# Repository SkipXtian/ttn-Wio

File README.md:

# GCLora Wio

An Open source weather station that reports tempurature, humidity, barometric pressure and has a RJ11 plug to suit a WH Series tipping bucket rain guage. It has a RFM96 Radio module mounted on the back, transmitting in the 915 - 928 MHz band.</p>

BME280 I2C Address is 0x76<br>
Rain Gauge is on Pin 7 (INT4)<br>

The Arduino example is to connect this Weather station to "The Things Network" through crowd sourced Gateways.
To see a list of gateways head to https://www.thethingsnetwork.org/map </p>

Instructions:

Clone this repo into a directory,<br>
Locate the secrets.h.template file in Arduino/ttn-Wio/<br>
Copy secrets.h.template -> secrets.h and copy details from your TTN console.<br>

This code depends on the lmic library - please make sure you use the version from https://github.com/secluded/arduino-lmic as we made a couple of small changes.
Remove all debugging from config.h for it to compile small enough.

Upload using the Arduino IDE the "Lilypad Arduino USB" board.

In your TTN console you should see data start to arrive. The example is configured to transmit every 5 minutes. You can change this in ttn_Wio.ino, look for TX_INTERVAL = 300; Unit is seconds.

The data should appear in this format: <br>
"32 36 32 38 2C 31 30 31 38 34 36 2C 35 35 34 33 2C 30" Which translates to: <br>
  2  6  2  8  ,  1  0  1  8  4  6  ,  5  5  4  3  ,  0<br>
26.28degress C,      1018.46hPa    ,55.43% Humidity, 0 Rain Ticks

The Tempurature,Barometric and Humidity are divided by 100 to give the decimal places.
Rain Ticks is the count of Rain bucket tipping, multiplying this by 0.2794 will give you rainfall in mm.
We left the processing of Rain for the purpose of indoor use where the sensor might be counting door usage, etc.

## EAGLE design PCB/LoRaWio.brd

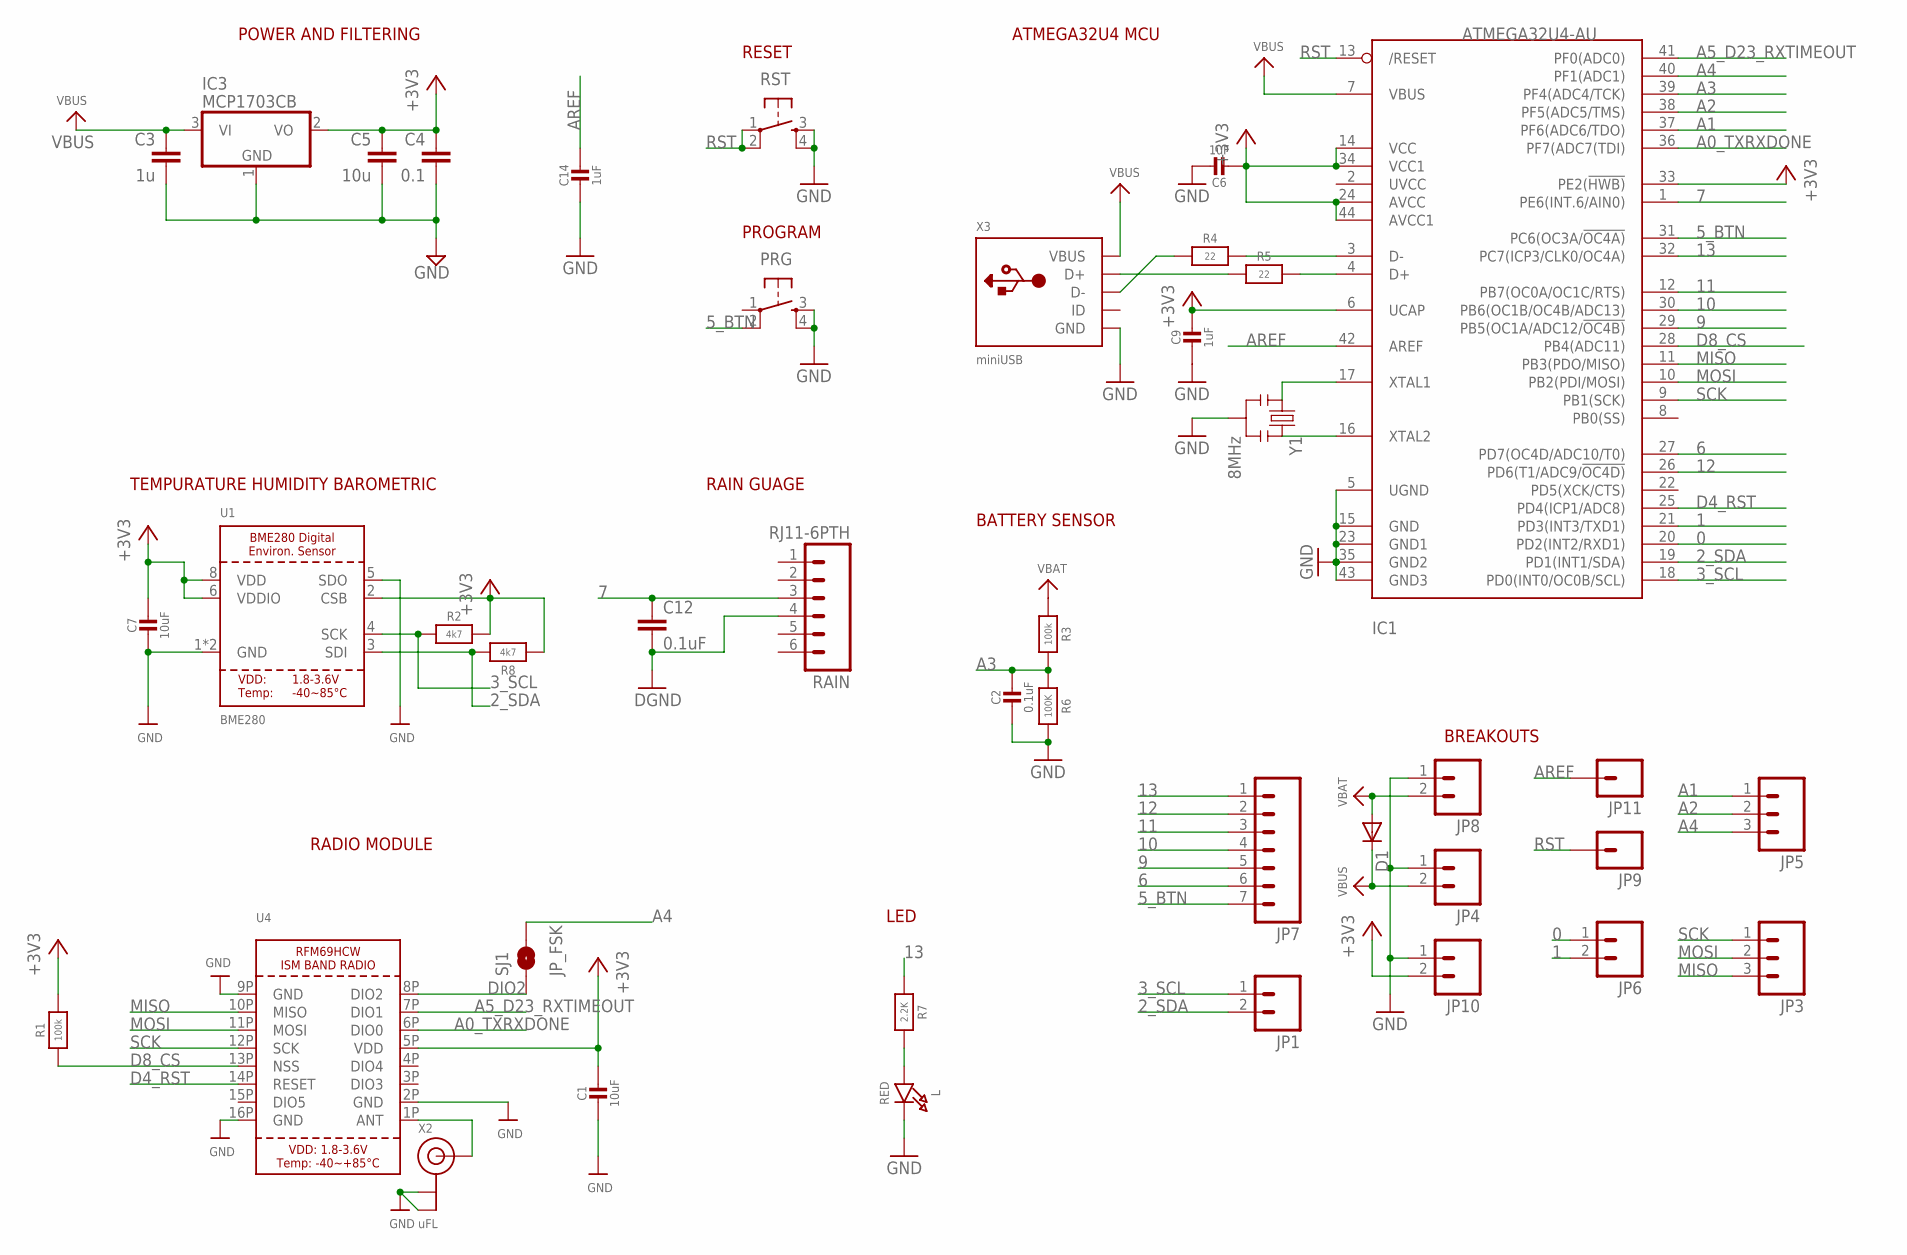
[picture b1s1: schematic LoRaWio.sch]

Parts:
C1, C7: 10uF; 0805-NO
C2: 0.1uF; 0805-NO
C3: 1u; 0805
C4: 0.1; 0805
C5: 10u; 0805-CAP
C6, C9, C14: 1uF; 0805-NO
C12: 0.1uF; 0805
D1: DIODESOD; SOD-323
IC1: ATMEGA32U4-AU; TQFP44
IC3: MCP1703CB; SOT23
JP1, JP4, JP6, JP8, JP10: M021X02_NO_SILK; 1X02_NO_SILK
JP3, JP5: M031X03_NO_SILK; 1X03_NO_SILK
JP7: M07; 1X07
JP9, JP11: M01PTH_NO_SILK_YES_STOP; 1X01_NO_SILK
L: RED; CHIPLED_0805_NOOUTLINE
PRG: TAC_SWITCHSMD; TACTILE_SWITCH_SMD
R1, R3: 100k; 0805-NO@1
R2, R8: 4k7; 0805-NO@1
R4, R5: 22; 0805-NO@1
R6: 100K; 0805-NO@1
R7: 2.2K; 0805-NO@1
RAIN: RJ11-6PTH; RJ11-6
RST: TAC_SWITCHSMD; TACTILE_SWITCH_SMD
SJ1: JP_FSK; SPARKFUN-PASSIVES_SJ_2S-NO
U1: BME280
U4: RFM69HCW_SMT; RFMHCW_SMT
X2: uFL; U.FL
X3: miniUSB; USB-MINIB_LARGER
Y1: 8MHz; RESONATOR-SMD

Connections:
0: IC1.20 (PD2(INT2/RXD1)), JP6.1
1: IC1.21 (PD3(INT3/TXD1)), JP6.2
2_SDA: IC1.19 (PD1(INT1/SDA)), JP1.2, R8.2, U1.3 (SDI)
3_SCL: IC1.18 (PD0(INT0/OC0B/SCL)), JP1.1, R2.1, U1.4 (SCK)
5_BTN: IC1.31 (PC6(OC3A/!OC4A)), JP7.7, PRG.2
6: IC1.27 (PD7(OC4D/ADC10/T0)), JP7.6
7: C12.1, IC1.1 (PE6(INT.6/AIN0)), RAIN.3
9: IC1.29 (PB5(OC1A/ADC12/!OC4B)), JP7.5
10: IC1.30 (PB6(OC1B/OC4B/ADC13)), JP7.4
11: IC1.12 (PB7(OC0A/OC1C/RTS)), JP7.3
12: IC1.26 (PD6(T1/ADC9/!OC4D)), JP7.2
13: IC1.32 (PC7(ICP3/CLK0/OC4A)), JP7.1, R7.1
+3V3: C1.1, C4.1, C5.1, C6.2, C7.1, C9.1, IC1.6 (UCAP), IC1.14 (VCC), IC1.24 (AVCC), IC1.33 (PE2(!HWB)), IC1.34 (VCC1), IC1.44 (AVCC1), IC3.2 (VO), JP10.2, R1.2, R2.2, R8.1, U1.2 (CSB), U1.6 (VDDIO), U1.8 (VDD), U4.5P (VDD)
A0_TXRXDONE: IC1.36 (PF7(ADC7(TDI)), U4.6P (DIO0)
A1: IC1.37 (PF6(ADC6/TDO)), JP5.1
A2: IC1.38 (PF5(ADC5/TMS)), JP5.2
A3: C2.1, IC1.39 (PF4(ADC4/TCK)), R3.2, R6.1
A4: IC1.40 (PF1(ADC1)), JP5.3, SJ1.2
A5_D23_RXTIMEOUT: IC1.41 (PF0(ADC0)), U4.7P (DIO1)
ANT: U4.1P (ANT), X2.3 (SIGNAL)
AREF: C14.1, IC1.42 (AREF), JP11.1
D4_RST: IC1.25 (PD4(ICP1/ADC8)), U4.14P (RESET)
D8_CS: IC1.28 (PB4(ADC11)), R1.1, U4.13P (NSS)
D+: IC1.4 (D+), R5.2
D-: IC1.3 (D-), R4.2
DIO2: SJ1.1, U4.8P (DIO2)
GND: C1.2, C2.2, C3.2, C4.2, C5.2, C6.1, C7.2, C9.2, C12.2, C14.2, IC1.5 (UGND), IC1.15 (GND), IC1.23 (GND1), IC1.35 (GND2), IC1.43 (GND3), IC3.1 (GND), JP4.1, JP8.1, JP10.1, L.C, PRG.3, PRG.4, R6.2, RAIN.4, RST.3, RST.4, U1.1 (GND), U1.5 (SDO), U1.7 (GND), U4.2P (GND), U4.9P (GND), U4.16P (GND), X2.1 (GND), X2.2 (GND), X3.GND, X3.GND1 (GND), X3.GND2 (GND), X3.GND3 (GND), X3.GND4 (GND), Y1.2
MISO: IC1.11 (PB3(PDO/MISO)), JP3.3, U4.10P (MISO)
MOSI: IC1.10 (PB2(PDI/MOSI)), JP3.2, U4.11P (MOSI)
unnamed: L.A, R7.2
unnamed: IC1.16 (XTAL2), Y1.3
unnamed: IC1.17 (XTAL1), Y1.1
unnamed: R5.1, X3.D+
unnamed: R4.1, X3.D-
RST: IC1.13 (/RESET), JP9.1, RST.1, RST.2
SCK: IC1.9 (PB1(SCK)), JP3.1, U4.12P (SCK)
VBAT: D1.2 (A), JP8.2, R3.1
VBUS: C3.1, D1.1 (C), IC1.7 (VBUS), IC3.3 (VI), JP4.2, X3.VBUS

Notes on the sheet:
POWER AND FILTERING
RESET
ATMEGA32U4 MCU
BREAKOUTS
RADIO MODULE
PROGRAM
RAIN GUAGE
TEMPURATURE HUMIDITY BAROMETRIC
LED
BATTERY SENSOR

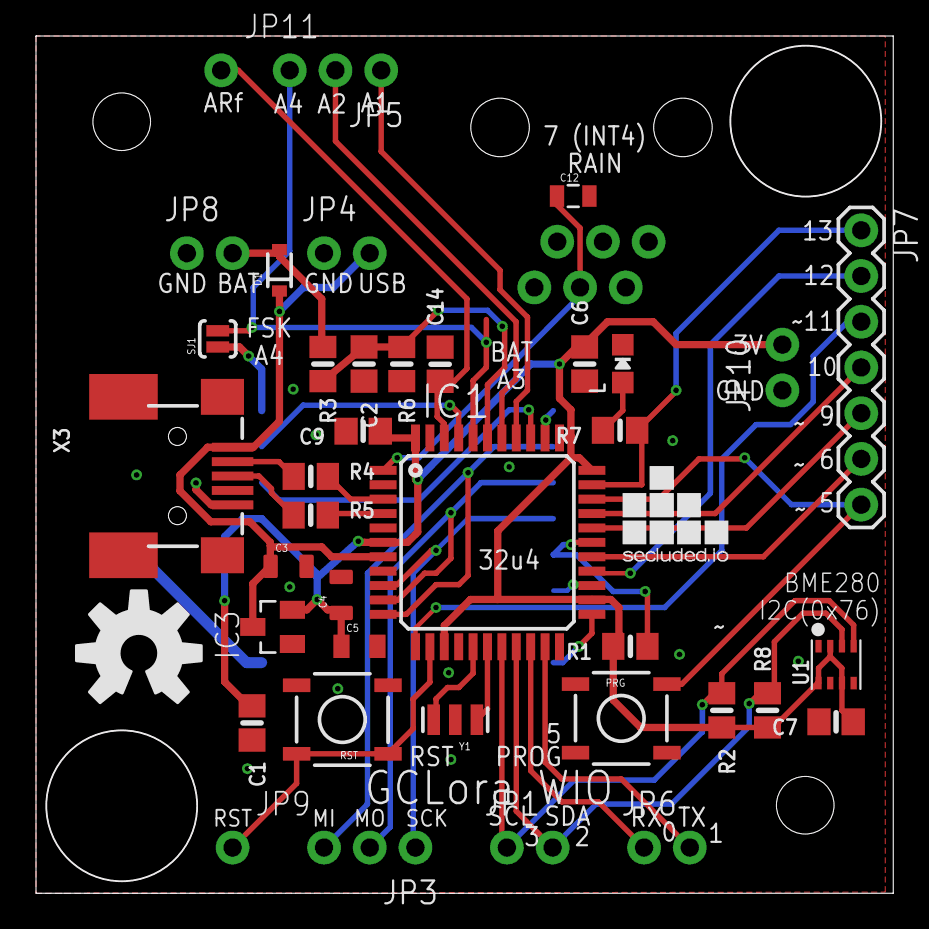
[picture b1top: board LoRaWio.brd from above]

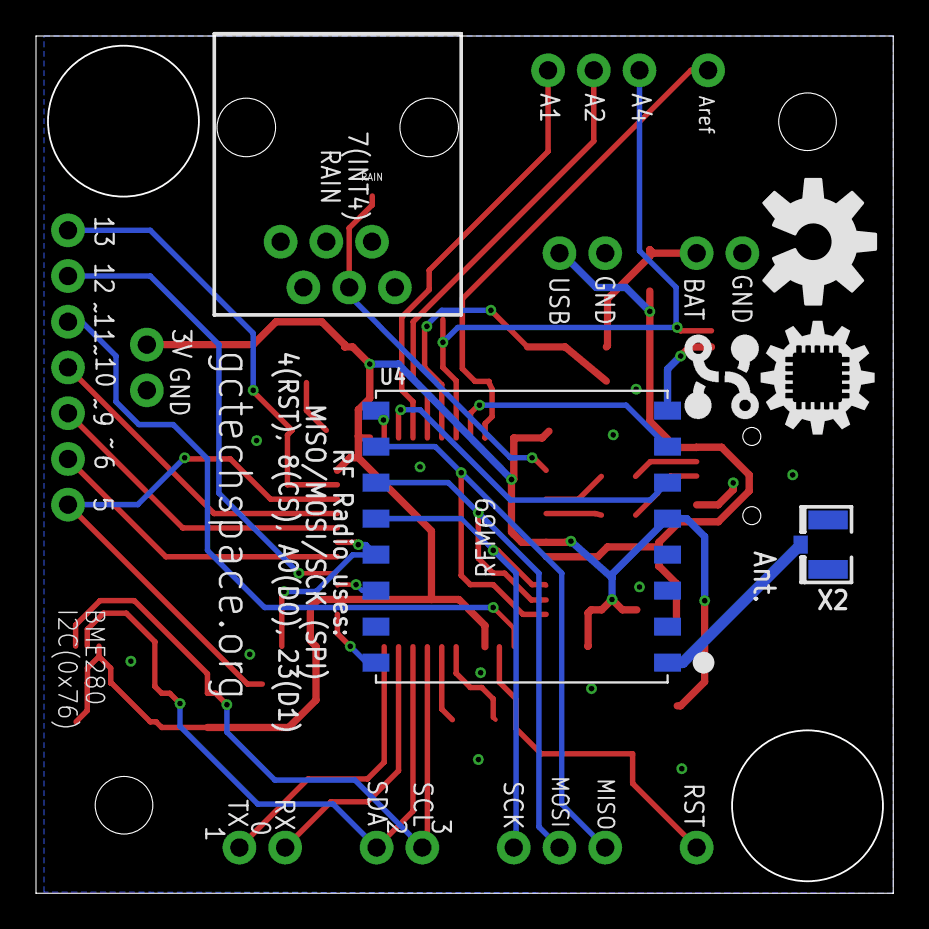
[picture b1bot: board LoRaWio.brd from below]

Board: 2 copper layers, 47.6 x 47.6 mm, 46 parts (6 on the bottom side), 38 nets.

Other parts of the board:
U$5, U$16: OSHW-LOGO-L
U$6: ESPDUINO_LOGO_5MM
U$7: SECLUDED_5MM
U$15: ID_LOGO_X0.25

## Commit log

2017-04-05 Initial Upload
2017-04-05 setup gitignore and general tidy
2017-04-05 updated gitignore
2017-04-05 Cleaned up code
2017-04-06 Pulled the buildPacket out into the main ino page.
2017-04-20 Added PCB and cleaned directory structure
2017-05-08 Added Watchdog timer
2017-05-16 Changed the packet to use bytes instead of char array, decrease length from 22 bytes to 8. Also saves almost 1k of space

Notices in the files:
parts and their libraries:
microbuilder: This work is placed in the public domain, and may be freely used for commercial and non-commercial work with the following conditions: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
SparkFun: Licensing: CC v3.0 Share-Alike You are welcome to use this library for commercial purposes.
